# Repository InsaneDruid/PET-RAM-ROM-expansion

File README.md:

# PET RAM & ROM - a 32K expansion for the PET 2001-8

While there are solutions to upgrade a PET 2001 to more than 4 or 8 Kb of RAM and use option ROMs in the 0x9000, 0xA000 and 0xB000 address range, these expansions usually sit in the processor socket and completely isolate the CPU from the PET motherboard during RAM and ROM access, turning the PET board into an I/O-only solution. While this is fine from a technical standpoint, I feel it destroys the spirit of retro computing and keeps the machines running, especially since all PETs have *some* designated expansion slot.

The PET RAM and ROM expansion utilizes the 2001's RAM/ROM expansion slot to expand - not replace - memory from 4 or 8 to a full 32 KB and to provide up to 2 switchable banks of expansion ROMs for the 0x9000, 0xA000 and 0xB000 address range. 

The physical design of the PET RAM & ROM is inspired by the Nestar Basic ToolKit extension.

[Schematic](https://github.com/InsaneDruid/pet-ram-rom-expansion/blob/main/pet-ram-&-rom-expansion.pdf "open Schematic")  

[Bill of Materials](https://htmlpreview.github.io/?https://github.com/InsaneDruid/pet-ram-rom-expansion/blob/main/bom/pet-ram-&-rom-expansion_bom.html "open Bill of Materials")

## The RAM
A 62256 static RAM provides up to 28Kb of additional RAM, beginning at 0x1000 or 0x2000, selectable with the JP1 *4K* jumper:
* For PETs having 4K of on-board memory, bridge jumper *4K*
* For PETs with 8K memory, leave jumper *4K* open.

Note: The RAM expansion slot does not provide the SEL0 line, so at least 4k of PET onboard memory are required.

## The ROM
The ROM slot of the PET RAM & ROM can be populated with either RAM, battery backed RAM, EEPROMs or classic EPROMs giving the option of either fixed expansion ROMs or SOFTROM solutions.

### The EPROM option
The use of EPROMs is a cost-effective and simple method of equipping the PET with up to 2 banks of expansion ROMs in the 0x9000, 0xA000 and 0xB000 address range.

#### 27128 EPROM - provides one bank of 3 expansion ROMS.

* Prepare the ROM contents as follows:

| ROM address hex | ROM address dec | Content |
| :--- | ---: | ---: |
| 0x0000-0x0FFF | (0 - 4095) | unused |
| 0x1000-0x1FFF | (4096 - 8191) | 0x9000 expansion ROM |
| 0x2000-0x2FFF | (8192 - 12287) | 0xA000 expansion ROM |
| 0x3000-0x3FFF | (12288 - 16383) | 0xB000 expansion ROM |
	
#### 27256 EPROM - provides two banks of 3 expansion ROMS
* Install a switch between the pins of the ROM 14 header to switch between the 2 banks.
* Prepare the ROM contents as follows:

| ROM address hex | ROM address dec | Content |
| :--- | ---: | ---: |
| 0x0000-0x0FFF | (0 - 4095) | unused |
| 0x1000-0x1FFF | (4096 - 8191) | 0x9000 expansion ROM 1 |
| 0x2000-0x2FFF | (8192 - 12287) | 0xA000 expansion ROM 1 |
| 0x3000-0x3FFF | (12288 - 16383) | 0xB000 expansion ROM 1 |
| 0x4000-0x4FFF | (16384 - 20479) | unused                 |
| 0x5000-0x5FFF | (20480 - 24575) | 0x9000 expansion ROM 2 |
| 0x6000-0x6FFF | (24576 - 28671) | 0xA000 expansion ROM 2 |
| 0x7000-0x7FFF | (28672 - 32767) | 0xB000 expansion ROM 2 |

### The SOFTROM option
The use of SRAM or battery-backed, non-volatile SRAM with a size of 16kB or 32kB (e.g. 62256 SRAM or DS1230Y/AB non-volatile SRAM) offers a flexible solution that is ideal if the content of the expansion ROMs needs to change frequently.

16k x 8 RAM - provides one bank of 3 expansion SOFTROMS  
32k x 8 RAM - provides two banks of 3 expansion SOFTROMS.

* Install a switch between the pins of the *RAM WE* header to control the write enable line of the RAM.  
It is recommended to set this switch to open after loading the content into the SOFTROM.
* When using 32Kb RAM, install a switch between the pins of the *ROM 14* header to switch between the 2 banks.

Note: theoretical, EEPROMs can be used as well, though currently there is no viable EEprom programming software for BASIC2 available.

## The Firmware
The GAL16V8 (tested on ATF 16V8BQL15 PU) needs to be programmed with the [Firmware](https://github.com/InsaneDruid/pet-ram-rom-expansion/blob/main/firmware "goto firmware folder"). A TL866/T48 eprom burner will do the job. Its *not neccessary to enable *encrypt chip* or to set the *lock bit*.

## The power source
Unfortunately, the 2001's RAM/ROM expansion slot doesn't provide any power pins, as RAM expansions thought to have their own power regulators and feed directly from the 2001's transformer.
The PET RAM & ROM though can be powered directly from the 5V available on the second tape port.

## The printable Backshell
To protect the backside of the board, and cover the power connector on the tape port, 3d printable parts are available.

[Printable back shell on printables.com](https://www.printables.com/model/1219181-cbm-pet-2001-expansion-cover/ "Printable back shell on printables.com") 

[Printable power connector housing on printables.com](https://www.printables.com/model/1219232-commodore-petc64-tape-connector-cover/ "Printable tape connector housing on printables.com")   

## The License
This work is licensed under a Creative Commons Attribution-ShareAlike 4.0 International License.  
See https://creativecommons.org/licenses/by-sa/4.0/.

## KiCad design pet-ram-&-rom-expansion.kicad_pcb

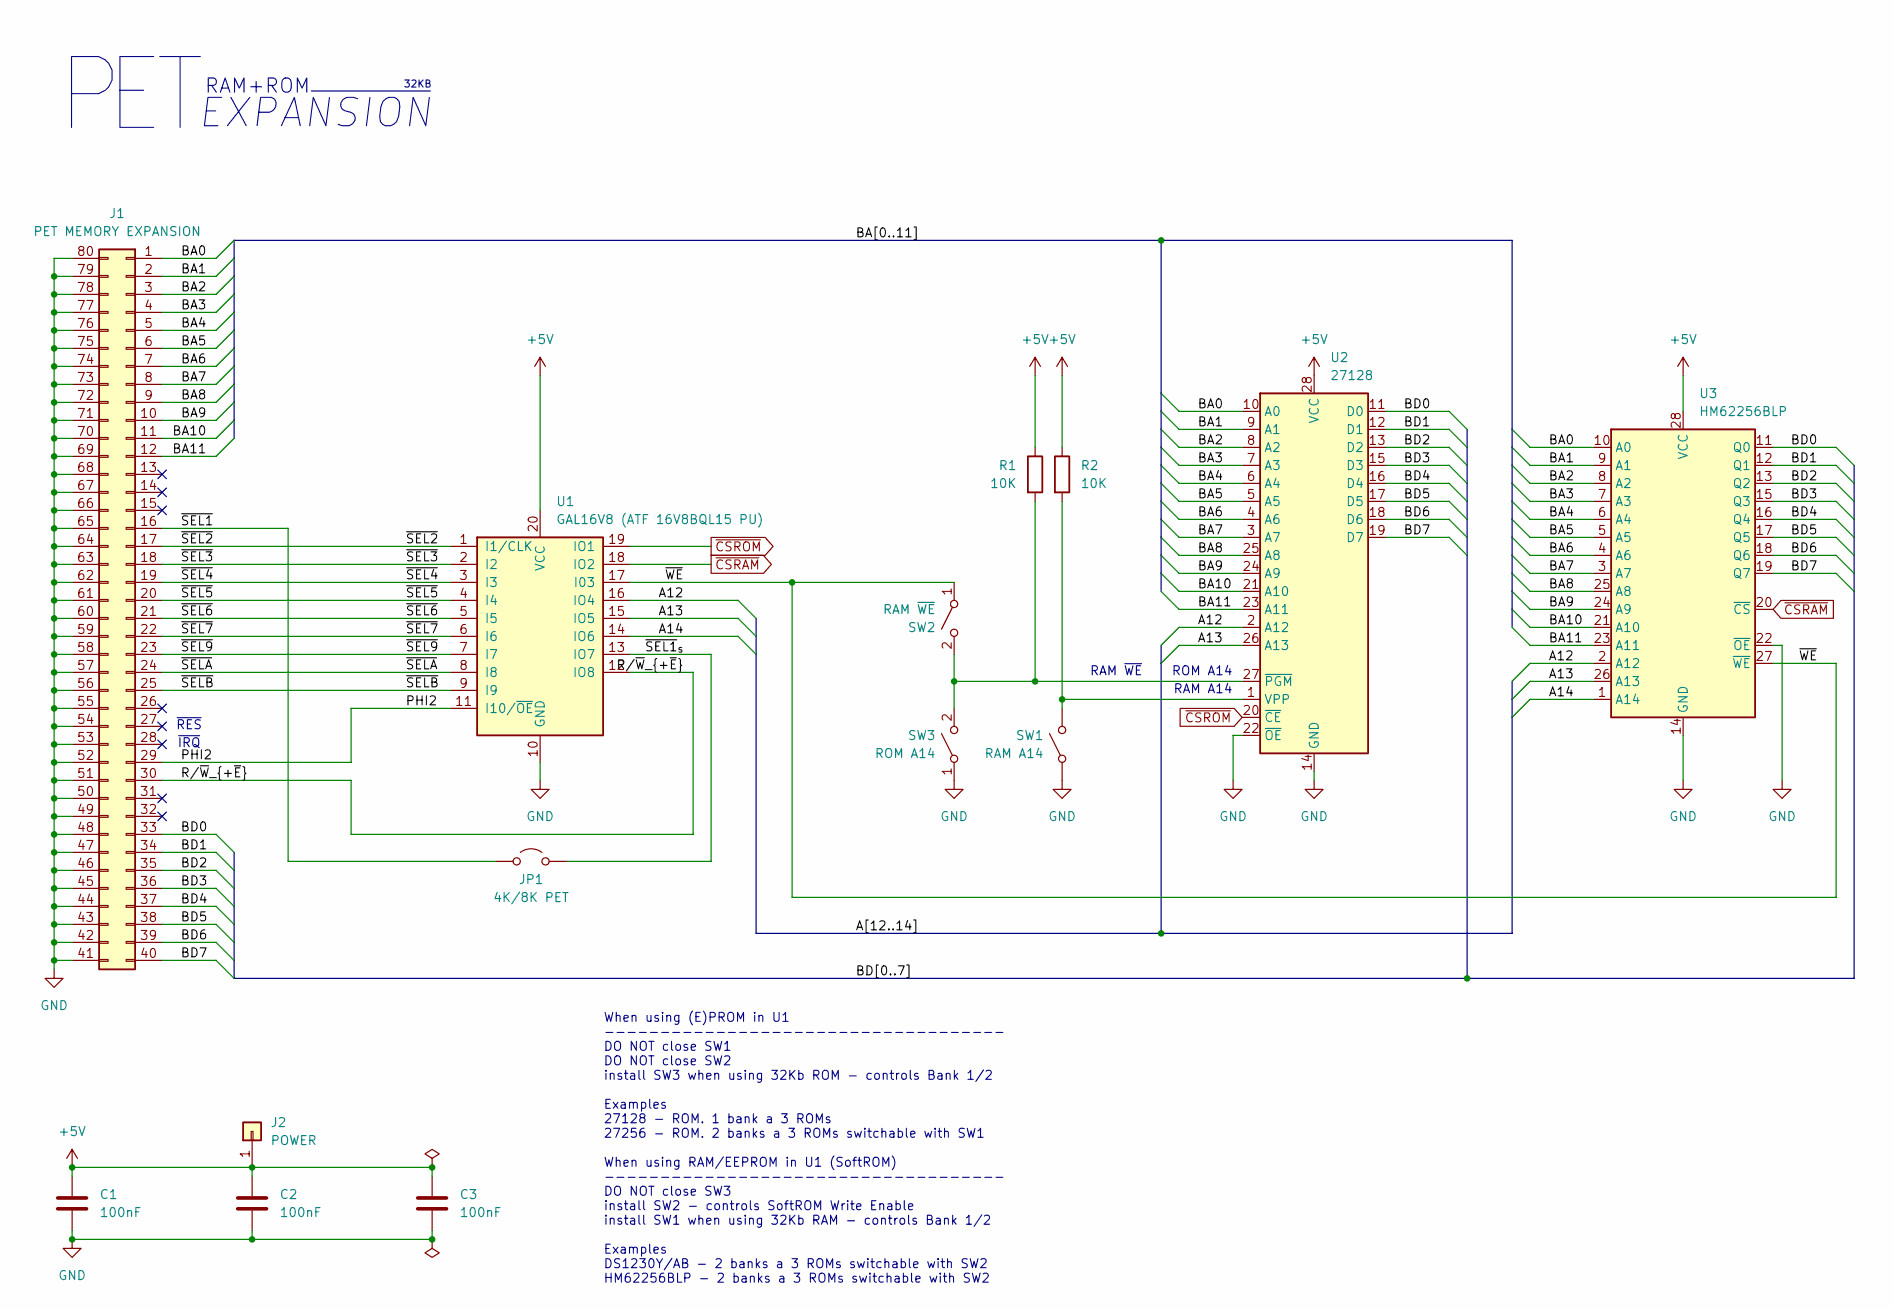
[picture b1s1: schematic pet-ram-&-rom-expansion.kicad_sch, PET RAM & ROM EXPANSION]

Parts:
C1, C2, C3: 100nF; C_Disc_D4.3mm_W1.9mm_P5.40mm
J1: PET MEMORY EXPANSION; pet expansion slot
J2: POWER; SolderWire-0.1sqmm_1x01_D0.4mm_OD1mm_Relief2x
JP1: 4K/8K PET; SolderJumper-2_P1.3mm_Open_RoundedPad1.0x1.5mm
R1, R2: 10K; R_Axial_DIN0204_L3.6mm_D1.6mm_P7.62mm_Horizontal
SW1: RAM A14; PinHeader_1x02_P2.54mm_Vertical
SW2: RAM ~{WE}; PinHeader_1x03_P2.54mm_Vertical
SW3: ROM A14; PinHeader_1x01_P2.54mm_Vertical
U1: GAL16V8 (ATF 16V8BQL15 PU); DIP-20_W7.62mm
U2: 27128; DIP-28_W15.24mm_Socket
U3: HM62256BLP; DIP-28_W15.24mm_Socket

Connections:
+5V: C1.1, C2.1, C3.1, J2.1, R1.1, R2.1, U1.20 (VCC), U2.28 (VCC), U3.28 (VCC)
/A12: U1.16 (IO4), U2.2 (A12), U3.2 (A12)
/A13: U1.15 (IO5), U2.26 (A13), U3.26 (A13)
/A14: U1.14 (IO6), U3.1 (A14)
/BA0: J1.1, U2.10 (A0), U3.10 (A0)
/BA1: J1.2, U2.9 (A1), U3.9 (A1)
/BA2: J1.3, U2.8 (A2), U3.8 (A2)
/BA3: J1.4, U2.7 (A3), U3.7 (A3)
/BA4: J1.5, U2.6 (A4), U3.6 (A4)
/BA5: J1.6, U2.5 (A5), U3.5 (A5)
/BA6: J1.7, U2.4 (A6), U3.4 (A6)
/BA7: J1.8, U2.3 (A7), U3.3 (A7)
/BA8: J1.9, U2.25 (A8), U3.25 (A8)
/BA9: J1.10, U2.24 (A9), U3.24 (A9)
/BA10: J1.11, U2.21 (A10), U3.21 (A10)
/BA11: J1.12, U2.23 (A11), U3.23 (A11)
/BD0: J1.33, U2.11 (D0), U3.11 (Q0)
/BD1: J1.34, U2.12 (D1), U3.12 (Q1)
/BD2: J1.35, U2.13 (D2), U3.13 (Q2)
/BD3: J1.36, U2.15 (D3), U3.15 (Q3)
/BD4: J1.37, U2.16 (D4), U3.16 (Q4)
/BD5: J1.38, U2.17 (D5), U3.17 (Q5)
/BD6: J1.39, U2.18 (D6), U3.18 (Q6)
/BD7: J1.40, U2.19 (D7), U3.19 (Q7)
/PHI2: J1.29, U1.11 (I10/~OE)
/R/~W_{+~E}: J1.30, U1.12 (IO8)
/~SEL1: J1.16, JP1.1 (A)
/~SEL1_{s}: JP1.2 (B), U1.13 (IO7)
/~SEL2: J1.17, U1.1 (I1/CLK)
/~SEL3: J1.18, U1.2 (I2)
/~SEL4: J1.19, U1.3 (I3)
/~SEL5: J1.20, U1.4 (I4)
/~SEL6: J1.21, U1.5 (I5)
/~SEL7: J1.22, U1.6 (I6)
/~SEL9: J1.23, U1.7 (I7)
/~SELA: J1.24, U1.8 (I8)
/~SELB: J1.25, U1.9 (I9)
/~WE: SW2.1 (A), U1.17 (I03), U3.27 (~WE)
GND: C1.2, C2.2, C3.2, J1.41, J1.42, J1.43, J1.44, J1.45, J1.46, J1.47, J1.48, J1.49, J1.50, J1.51, J1.52, J1.53, J1.54, J1.55, J1.56, J1.57, J1.58, J1.59, J1.60, J1.61, J1.62, J1.63, J1.64, J1.65, J1.66, J1.67, J1.68, J1.69, J1.70, J1.71, J1.72, J1.73, J1.74, J1.75, J1.76, J1.77, J1.78, J1.79, J1.80, SW1.1 (A), SW3.1 (A), U1.10 (GND), U2.14 (GND), U2.22 (~OE), U3.14 (GND), U3.22 (~OE)
unnamed: R2.2, SW1.2 (B), U2.1 (VPP)
unnamed: R1.2, SW2.2 (B), SW3.2 (B), U2.27 (~PGM)
~CSRAM: U1.18 (IO2), U3.20 (~CS)
~CSROM: U1.19 (IO1), U2.20 (~CE)

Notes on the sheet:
ROM A14
RAM A14
32KB
RAM ~{WE}
When using (E)PROM in U1 ------------------------------------ DO NOT close SW1 DO NOT close SW2 install SW3 when using 32Kb ROM - controls Bank 1/2 Examples 27128 - ROM. 1 bank a 3 ROMs 27256 - ROM. 2 banks a 3 ROMs switchable with SW1 When using RAM/EEPROM in U1 (SoftROM) -------------------------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
~{RES}
EXPANSION
~{IRQ}
RAM+ROM

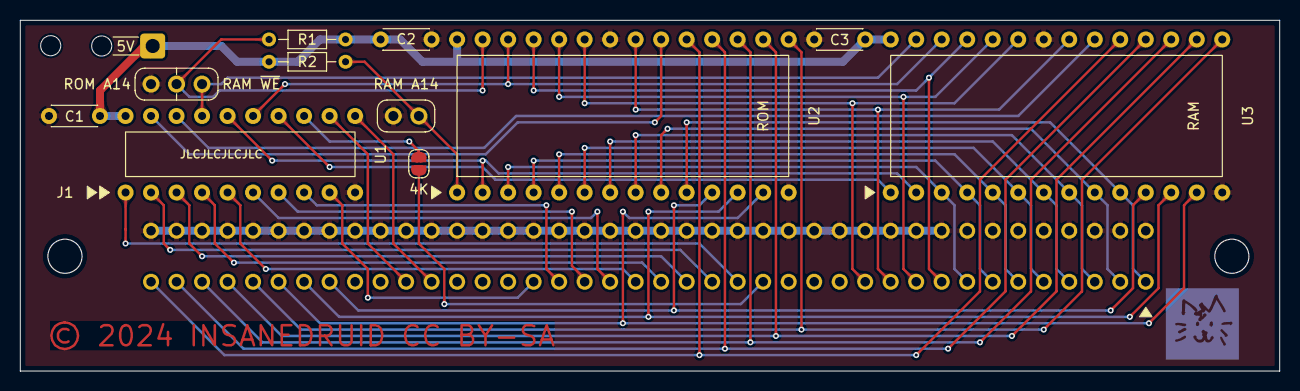
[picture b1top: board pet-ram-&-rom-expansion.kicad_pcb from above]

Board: 2 copper layers, 125.3 x 34.9 mm, 14 parts (0 on the bottom side), 43 nets.

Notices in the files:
pet-ram-&-rom-expansion.kicad_pcb:
© 2024
License: CC BY-SA 4.0
© 2024 INSANEDRUID CC BY-SA
